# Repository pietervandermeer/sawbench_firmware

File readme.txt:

The Sawbench Synthesizer firmware.

(c) Tasty Chips Electronics, 2014-2016

This code may be used to update your sawbench synth, using only an Arduino Uno 
(10 euro from China). The easiest way of doing things is to: 

1) install this archive in your arduino folder. On Mac that's mostly 
~/Documents/Arduino

2) start Arduino IDE

3) open sawbench_v3/sawbench_v3.ino

4) attach your arduino uno

5) upload. The firmware is now present on the Arduino's Atmega328P. 

6) open up the sawbench, and remove its atmega. 

7) replace the sawbench's Atmega with the one from the Arduino. Presto!

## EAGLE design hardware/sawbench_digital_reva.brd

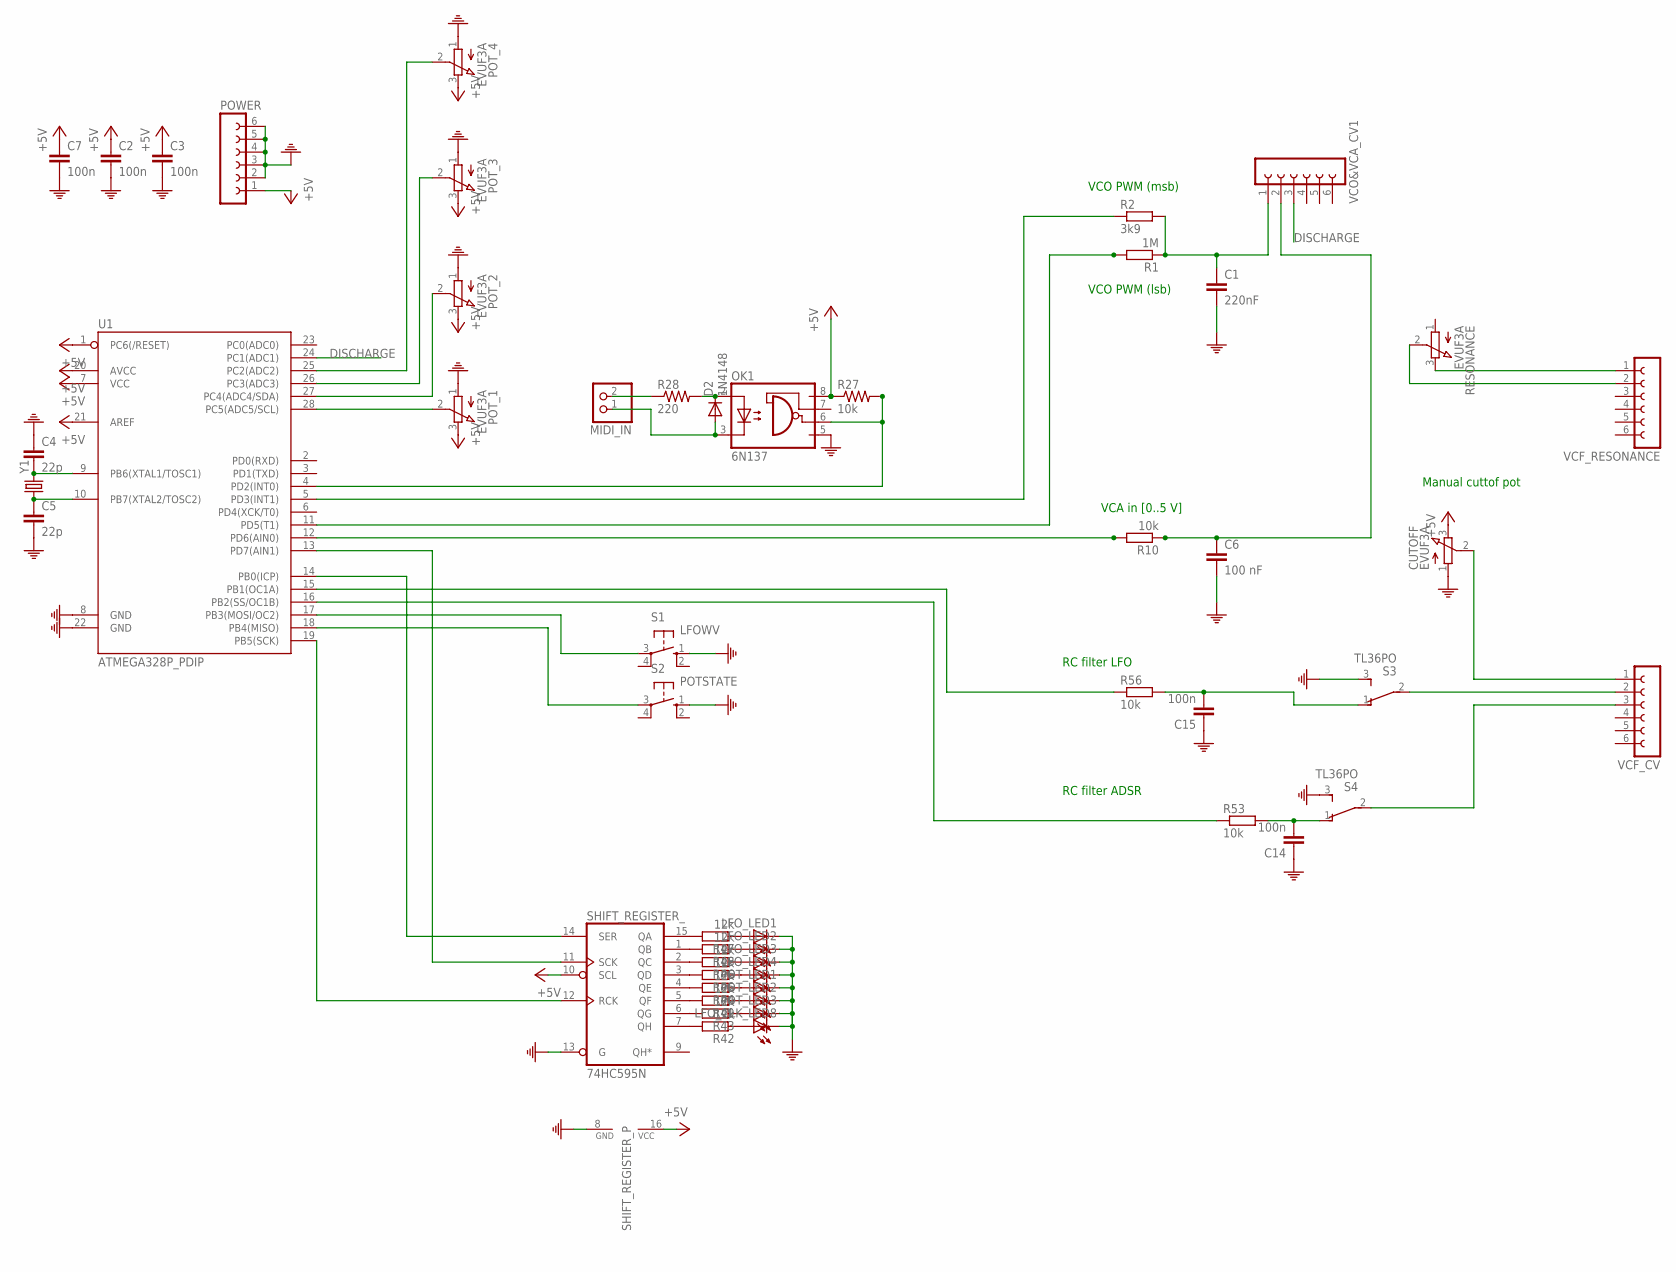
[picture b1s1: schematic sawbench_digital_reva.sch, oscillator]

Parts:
C1: 220nF; C050-024X044
C2, C3, C7, C14, C15: 100n; C025-024X044
C4, C5: 22p; C025-024X044
C6: 100 nF; C025-025X050
CUTOFF: EVUF3A; EVUF
D2: 1N4148; D-5
LFO_CLK_LED8: LED3MM
LFO_LED1, LFO_LED2, LFO_LED3, LFO_LED4: LED3MM
MIDI_IN: PINHD-1X2; 1X02
OK1: 6N137; DIL08
POT_1, POT_2, POT_3, POT_4: EVUF3A; EVUF
POT_LED1, POT_LED2, POT_LED3: LED3MM
POWER: FE06-1; FE06
R1: 1M; 0204/7
R2: 3k9; 0204/7
R10, R27, R53, R56: 10k; 0204/7
R28: 220; 0204/7
R42, R43, R44, R45, R46, R47, R48, R49: 12k; 0204/7
RESONANCE: EVUF3A; EVUF
S1: LFOWV; B3F-10XX(TASTYSWITCH)
S2: POTSTATE; B3F-10XX(TASTYSWITCH)
S3, S4: TL36PO; TL3XPO(TASTY_CHIPS_UPDATE)
SHIFT_REGISTER_: 74HC595N; DIL16
U1: ATMEGA328P_PDIP; DIL28-3
VCF_CV: FE06-1; FE06
VCF_RESONANCE: FE06-1; FE06
VCO&VCA_CV1: FE06-1; FE06
Y1: CRYSTALHC49S; HC49/S

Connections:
+5V: C2.1, C3.1, C7.1, CUTOFF.3 (E), OK1.8 (VCC), POT_1.3 (E), POT_2.3 (E), POT_3.3 (E), POT_4.3 (E), POWER.1, R27.1, SHIFT_REGISTER_.10 (SCL), SHIFT_REGISTER_.16 (VCC), U1.1 (PC6(/RESET)), U1.7 (VCC), U1.20 (AVCC), U1.21 (AREF)
DISCHARGE: U1.24 (PC1(ADC1)), VCO&VCA_CV1.3
unnamed: C1.1, R1.1, R2.2, VCO&VCA_CV1.1
unnamed: C6.1, R10.1, VCO&VCA_CV1.2
unnamed: R1.2, U1.11 (PD5(T1))
unnamed: S3.2, VCF_CV.2
unnamed: S4.2, VCF_CV.3
unnamed: OK1.6 (VO), R27.2, U1.4 (PD2(INT0))
unnamed: R2.1, U1.5 (PD3(INT1))
unnamed: POT_1.2 (S), U1.28 (PC5(ADC5/SCL))
unnamed: POT_4.2 (S), U1.25 (PC2(ADC2))
unnamed: POT_2.2 (S), U1.27 (PC4(ADC4/SDA))
unnamed: SHIFT_REGISTER_.11 (SCK), U1.13 (PD7(AIN1))
unnamed: POT_3.2 (S), U1.26 (PC3(ADC3))
unnamed: S1.3, U1.17 (PB3(MOSI/OC2))
unnamed: C4.2, U1.9 (PB6(XTAL1/TOSC1)), Y1.2
unnamed: C5.1, U1.10 (PB7(XTAL2/TOSC2)), Y1.1
unnamed: R10.2, U1.12 (PD6(AIN0))
unnamed: CUTOFF.2 (S), VCF_CV.1
unnamed: D2.C, OK1.2 (A), R28.2
unnamed: MIDI_IN.2, R28.1
unnamed: LFO_LED1.A, R47.1
unnamed: RESONANCE.3 (E), VCF_RESONANCE.1
unnamed: C14.2, R53.2, S4.1 (O)
unnamed: R42.2, SHIFT_REGISTER_.7 (QH)
unnamed: R43.2, SHIFT_REGISTER_.6 (QG)
unnamed: R44.2, SHIFT_REGISTER_.4 (QE)
unnamed: R45.2, SHIFT_REGISTER_.3 (QD)
unnamed: R46.2, SHIFT_REGISTER_.2 (QC)
unnamed: R47.2, SHIFT_REGISTER_.15 (QA)
unnamed: R48.2, SHIFT_REGISTER_.1 (QB)
unnamed: R49.2, SHIFT_REGISTER_.5 (QF)
unnamed: LFO_LED2.A, R48.1
unnamed: LFO_LED3.A, R46.1
unnamed: LFO_LED4.A, R45.1
unnamed: POT_LED1.A, R44.1
unnamed: POT_LED2.A, R49.1
unnamed: POT_LED3.A, R43.1
unnamed: LFO_CLK_LED8.A, R42.1
unnamed: SHIFT_REGISTER_.12 (RCK), U1.19 (PB5(SCK))
unnamed: SHIFT_REGISTER_.14 (SER), U1.14 (PB0(ICP))
unnamed: S2.3, U1.18 (PB4(MISO))
unnamed: C15.2, R56.2, S3.1 (O)
unnamed: R56.1, U1.15 (PB1(OC1A))
unnamed: R53.1, U1.16 (PB2(SS/OC1B))
unnamed: RESONANCE.2 (S), VCF_RESONANCE.2
unnamed: D2.A, MIDI_IN.1, OK1.3 (C)
PE: C1.2, C2.2, C3.2, C4.1, C5.2, C6.2, C7.2, C14.1, C15.1, CUTOFF.1 (A), LFO_CLK_LED8.K (C), LFO_LED1.K (C), LFO_LED2.K (C), LFO_LED3.K (C), LFO_LED4.K (C), OK1.5 (GND), POT_1.1 (A), POT_2.1 (A), POT_3.1 (A), POT_4.1 (A), POT_LED1.K (C), POT_LED2.K (C), POT_LED3.K (C), POWER.2, POWER.3, POWER.4, POWER.5, POWER.6, S1.1 (S), S2.1 (S), S3.3 (S), S4.3 (S), SHIFT_REGISTER_.8 (GND), SHIFT_REGISTER_.13 (G), U1.8 (GND), U1.22 (GND)

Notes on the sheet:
VCO PWM (msb)
VCO PWM (lsb)
VCA in [0..5 V]
RC filter LFO
RC filter ADSR
Manual cuttof pot

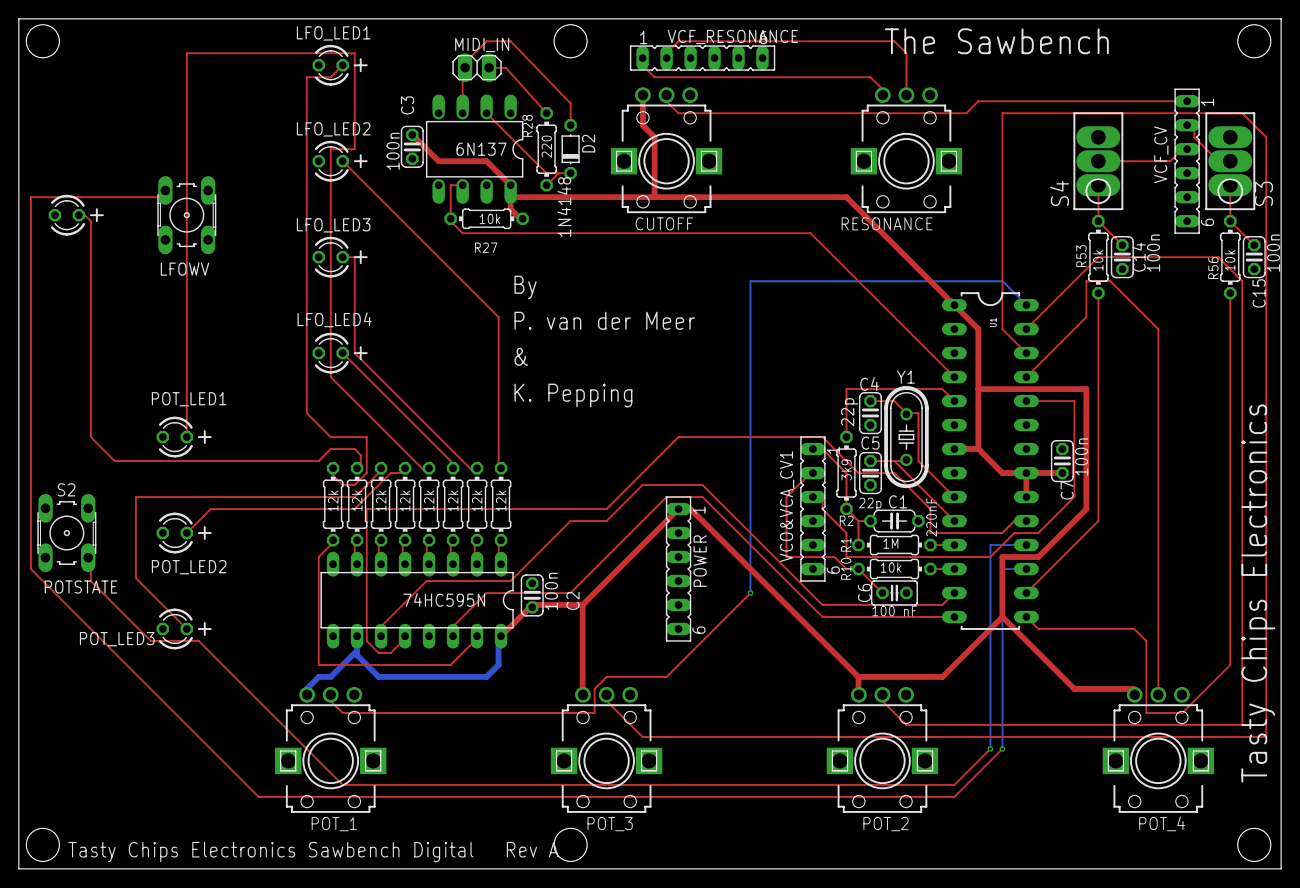
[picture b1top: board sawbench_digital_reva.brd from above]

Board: 2 copper layers, 133.7 x 90.0 mm, 52 parts (0 on the bottom side), 48 nets.

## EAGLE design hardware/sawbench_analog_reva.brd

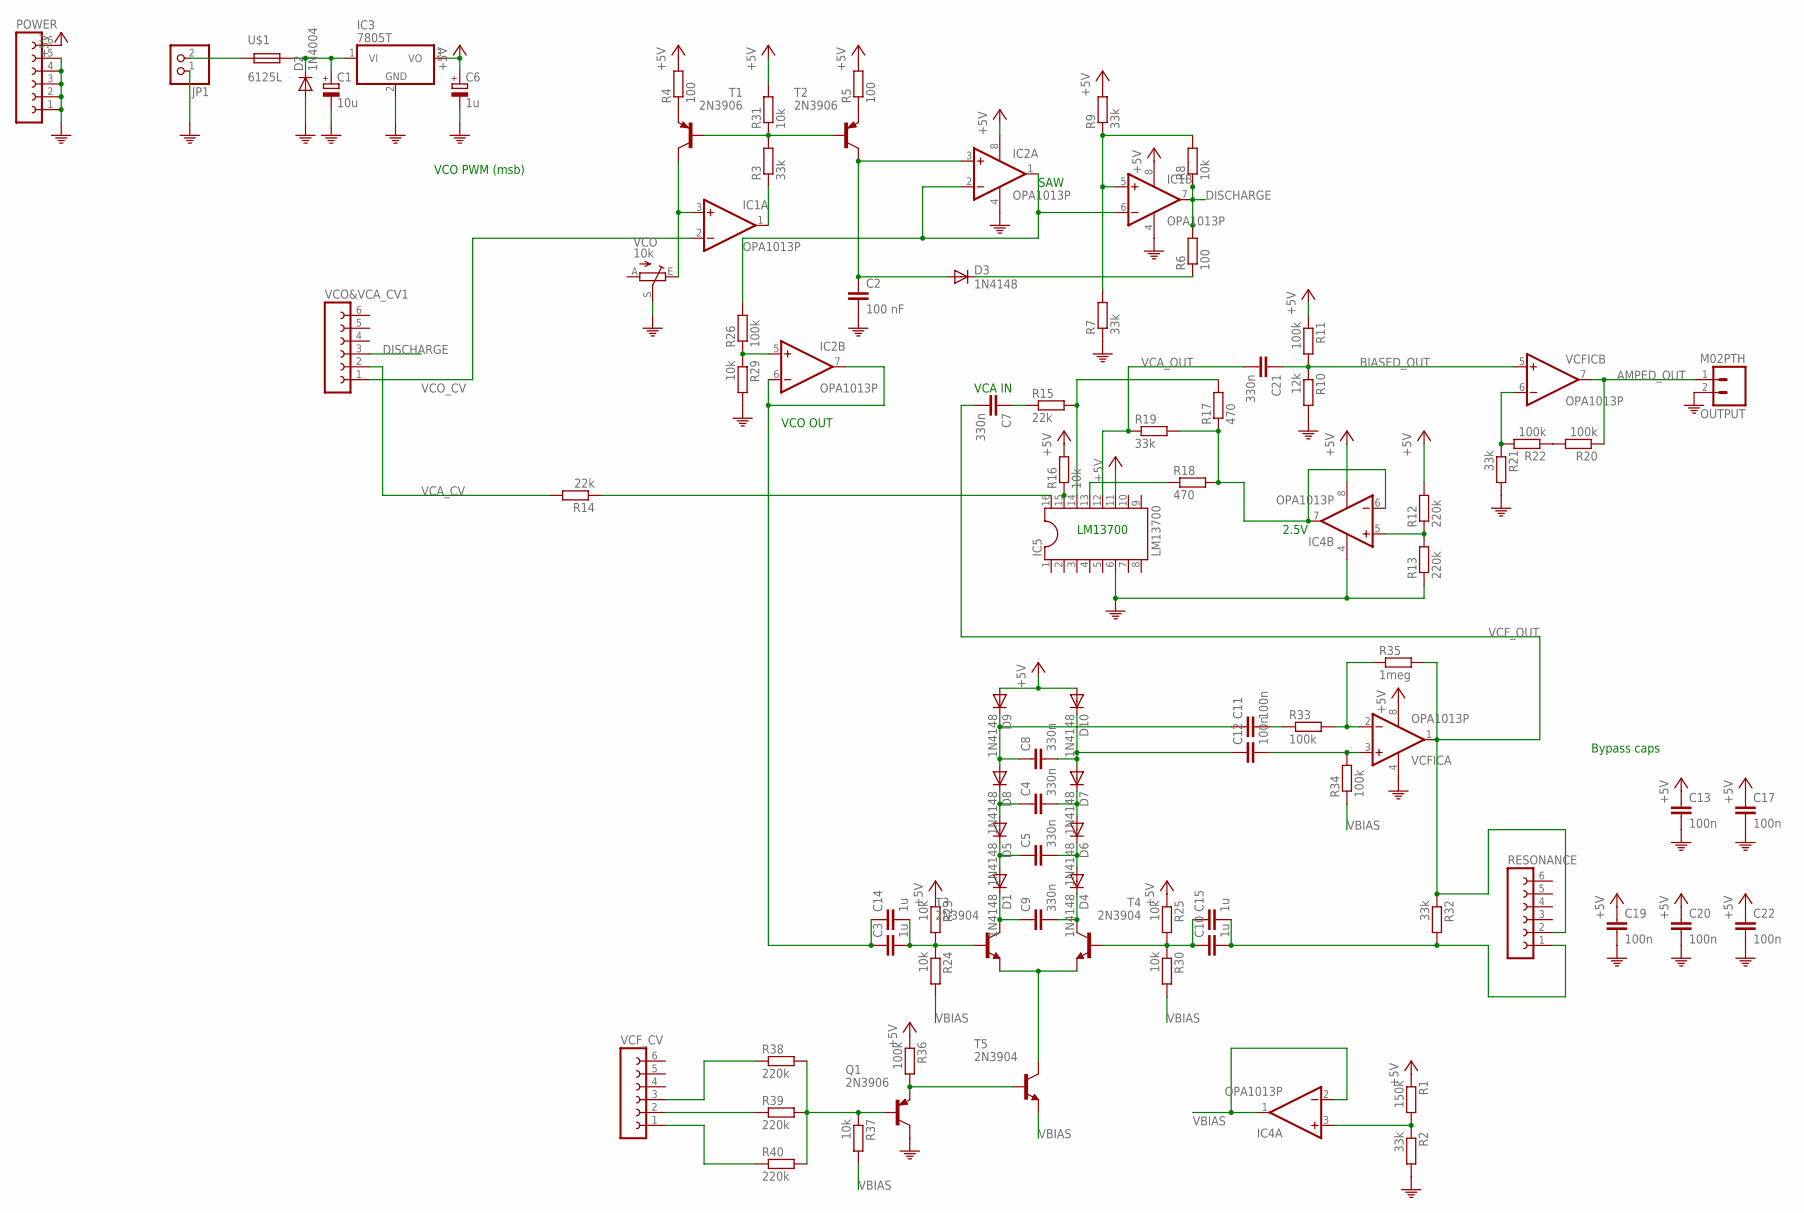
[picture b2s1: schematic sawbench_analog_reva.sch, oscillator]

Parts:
C1: 10u; E2,5-6
C2: 100 nF; C050-030X075
C3, C10, C14, C15: 1u; C050-024X044
C4, C5, C8, C9: 330n; C050-030X075
C6: 1u; E2,5-6
C7, C21: 330n; C050-024X044
C11, C12: 100n; C050-025X075
C13, C17, C19, C20, C22: 100n; C025-024X044
D1, D3, D4, D5, D6, D7, D8, D9, D10: 1N4148; D-5
D2: 1N4004; DO41-10
IC1, IC2, IC4: OPA1013P; DIL08
IC3: 7805T; TO220H
IC5: LM13700; DIL16
JP1: PINHD-1X2; 1X02
OUTPUT: M02PTH; 1X02
POWER: FE06-1; FE06
Q1: 2N3906; TO92-EBC
R1: 150k; 0204/7
R2, R3, R7, R9, R19, R21, R32: 33k; 0204/7
R4, R5, R6: 100; 0204/7
R8, R16, R23, R24, R25, R29, R30, R31, R37: 10k; 0204/7
R10: 12k; 0204/7
R11, R20, R22, R26, R33, R34, R36: 100k; 0204/7
R12, R13, R38, R39, R40: 220k; 0204/7
R14, R15: 22k; 0204/7
R17, R18: 470; 0204/7
R35: 1meg; 0204/7
RESONANCE: FE06-1; FE06
T1, T2: 2N3906; TO92-EBC
T3, T4, T5: 2N3904; TO92-EBC
U$1: 6125L
VCFIC: OPA1013P; DIL08
VCF_CV: FE06-1; FE06
VCO: 10k; RJ9W
VCO&VCA_CV1: FE06-1; FE06

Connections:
+5V: C6.+, C13.1, C17.1, C19.1, C20.1, C22.1, D9.A, D10.A, IC1.8 (V+), IC2.8 (V+), IC3.3 (VO), IC4.8 (V+), IC5.11, POWER.6, R1.1, R4.2, R5.2, R9.2, R11.1, R12.2, R16.2, R23.1, R25.1, R31.2, R36.1, VCFIC.8 (V+)
AMPED_OUT: OUTPUT.1, R20.1, VCFIC.7 (OUT)
BIASED_OUT: C21.1, R10.1, R11.2, VCFIC.5 (+IN)
DISCHARGE: IC1.7 (OUT), R6.2, R8.1, VCO&VCA_CV1.3
unnamed: R20.2, R22.1
unnamed: IC1.3 (+IN), T1.C, VCO.E
unnamed: C3.1, C14.1, IC2.6 (-IN), IC2.7 (OUT)
unnamed: C2.1, D3.A, IC2.3 (+IN), T2.C
unnamed: IC1.1 (OUT), R3.1
unnamed: R3.2, R31.1, T1.B, T2.B
unnamed: R4.1, T1.E
unnamed: R5.1, T2.E
unnamed: IC5.16, R14.1
unnamed: IC1.6 (-IN), IC2.1 (OUT), IC2.2 (-IN), R26.2
unnamed: R40.1, VCF_CV.1
unnamed: R39.1, VCF_CV.2
unnamed: IC1.5 (+IN), R7.2, R8.2, R9.1
unnamed: JP1.2, U$1.P$1 (1)
unnamed: D3.C, R6.1
unnamed: R38.1, VCF_CV.3
unnamed: IC4.3 (+IN), R1.2, R2.1
unnamed: IC4.5 (+IN), R12.1, R13.2
unnamed: IC5.13, R18.1
unnamed: IC5.14, R15.2, R17.2
unnamed: IC5.15, R16.1
unnamed: R21.1, R22.2, VCFIC.6 (-IN)
unnamed: IC4.6 (-IN), IC4.7 (OUT), R17.1, R18.2, R19.2
unnamed: C3.2, C14.2, R23.2, R24.1, T3.B
unnamed: T3.E, T4.E, T5.C
unnamed: C9.1, D1.C, T3.C
unnamed: C9.2, D4.C, T4.C
unnamed: C5.1, D1.A, D5.C
unnamed: C1.+, D2.C, IC3.1 (VI), U$1.P$2 (2)
unnamed: IC2.5 (+IN), R26.1, R29.1
unnamed: C7.1, R15.1
unnamed: C4.1, D5.A, D8.C
unnamed: C8.1, C11.1, D8.A, D9.C
unnamed: C8.2, C12.1, D7.A, D10.C
unnamed: C4.2, D6.A, D7.C
unnamed: C5.2, D4.A, D6.C
unnamed: C10.1, C15.1, R25.2, R30.1, T4.B
unnamed: C10.2, C15.2, R32.2, RESONANCE.1
unnamed: C11.2, R33.1
unnamed: C12.2, R34.2, VCFIC.3 (+IN)
unnamed: R33.2, R35.1, VCFIC.2 (-IN)
unnamed: Q1.E, R36.2, T5.B
unnamed: Q1.B, R37.1, R38.2, R39.2, R40.2
PE: C1.-, C2.2, C6.-, C13.2, C17.2, C19.2, C20.2, C22.2, D2.A, IC1.4 (V-), IC2.4 (V-), IC3.2 (GND), IC4.4 (V-), IC5.6, JP1.1, OUTPUT.2, POWER.1, POWER.2, POWER.3, POWER.4, POWER.5, Q1.C, R2.2, R7.1, R10.2, R13.1, R21.2, R29.2, VCFIC.4 (V-), VCO.S
VBIAS: IC4.1 (OUT), IC4.2 (-IN), R24.2, R30.2, R34.1, R37.2, T5.E
VCA_CV: R14.2, VCO&VCA_CV1.2
VCA_OUT: C21.2, IC5.12, R19.1
VCF_OUT: C7.2, R32.1, R35.2, RESONANCE.2, VCFIC.1 (OUT)
VCO_CV: IC1.2 (-IN), VCO&VCA_CV1.1

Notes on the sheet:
VCO PWM (msb)
SAW
LM13700
2.5V
VCO OUT
VCA IN
Bypass caps

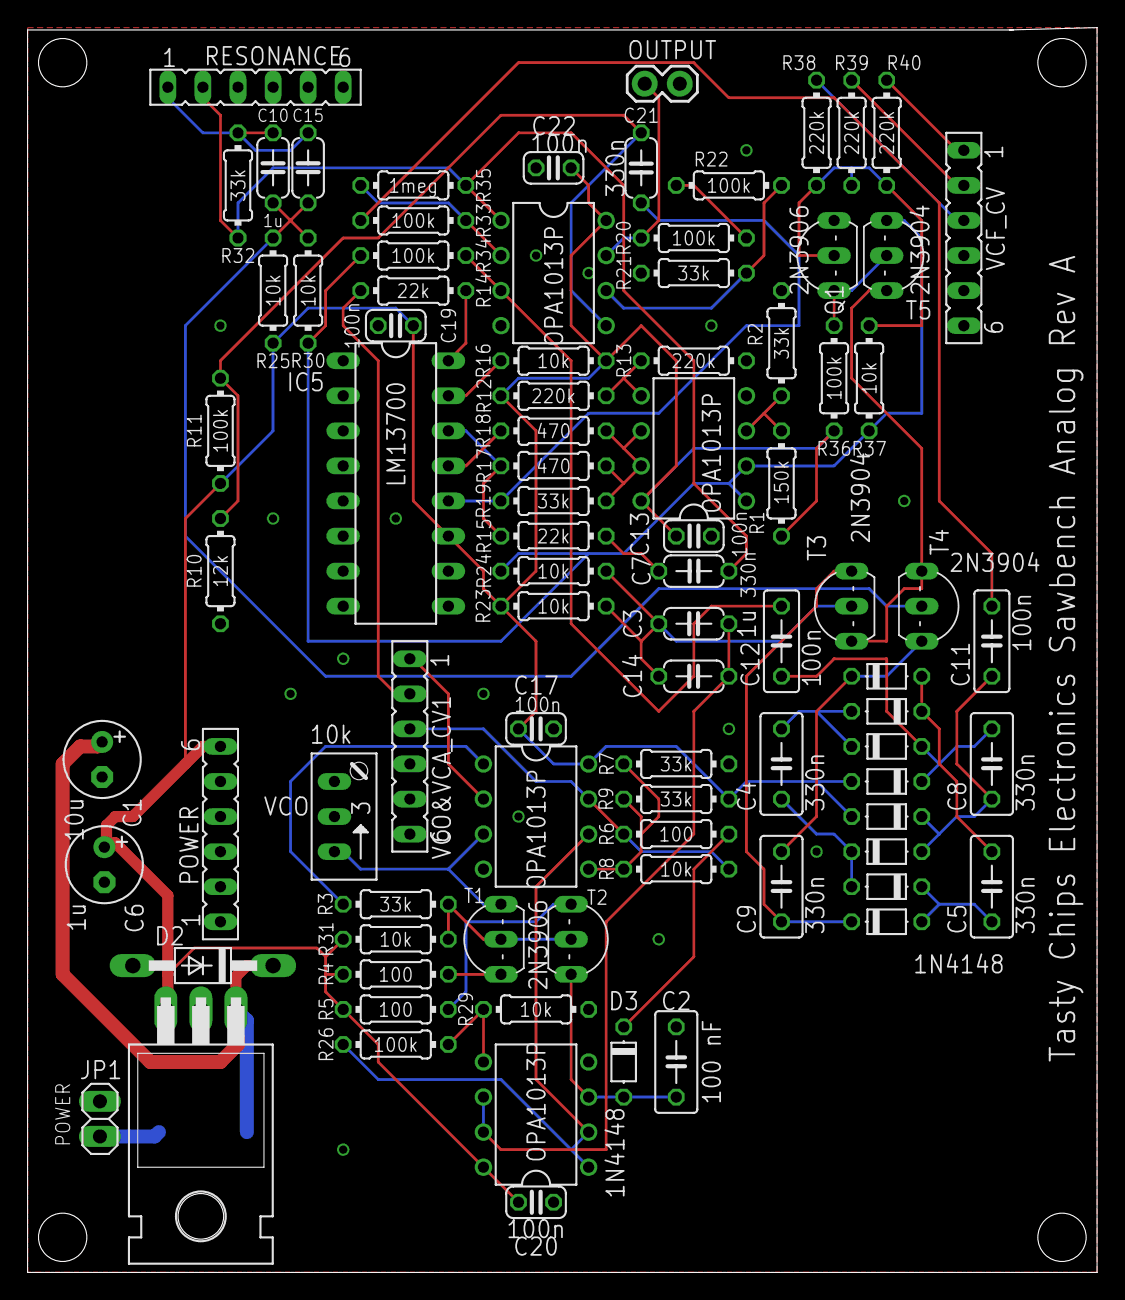
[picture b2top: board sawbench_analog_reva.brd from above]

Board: 2 copper layers, 77.5 x 90.2 mm, 88 parts (1 on the bottom side), 53 nets.

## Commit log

2014-12-20 initial commit, including koen's new sketch and PiggyLFO class.
2014-12-20 attempt to let MIDI and LFO not bite eachother.
2014-12-20 added VCF ENV. adapted Koen's LFO code to DDS in timed loop. MIDI IN seems fine again.
2015-01-09 lfo button pin changed. introduced gpio debugging again.
2015-01-18 unoptimized and non-midi version of sawbench firmware.
2015-01-18 optimized to one analogRead() using round robin.
2015-01-19 more optimized version _newer.ino.. still not good enough.
2015-01-19 a whattheheck. let's just run the loop at 1 kHz. oh yeah, pots now have nice negcube curves.
2015-01-19 callbacks for pot readouts.
2015-01-19 lfo speed for sample and hold.
2015-01-20 midi ccs for all 12 pot functions. vcf keyboard tracking + midi cc. lfo led with soft pwm.
2015-01-20 fixed lfo crap. addressing with signed offset where unsigned is passed. yep.
2015-01-20 lfo speed via midi now scaled correctly.
2015-01-25 fixed potstate behaviour. midi can now always interrupt it. pots can always override midi, and their initial behavior after reset is fixed. lfo led now optional (because of the background noise it ma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
2015-01-25 and now for real.. pot+midi interaction has been fixed, for the last ultimate time. also the potstate code has been cleaned up and optimized.
2015-01-26 lfo type now selectable using midi.
2015-02-11 added calibration script for J unit.
2015-02-11 added lfo led disable featuring (hold down lfo button 3 seconds). added k unit calibration script.
2015-02-16 first version of the firmware that uses self-calibration. requires a trace (or patch wire) from vco buffer output to arduino pin 4.
2015-02-17 shortened calibration and also made it more reliable. boot now takes 3 seconds. parameters now have defaults. vcf env overflow bug fixed. lfo mode is sine wave, by default.
2015-02-20 introductory light show
2015-03-29 variable glide, legato (with cc on/off).
2015-03-30 looping adsr, independent for vca and vcf. config via cc. sustain is skipped when looping.
2015-04-17 added sawbench_v3.ino.. lol.
2015-07-24 potential fix for midi problems. all midi bytes are now handled by the statemachine, at least.
2015-08-19 added readme.txt with installation details. added history.txt.
2016-01-05 new adsr curve and precision: shorter attacks, while retaining full adsr range. exponential adsr as well. unit tests check out fine, fw compiles. not yet tested live..
2016-10-05 midi beat fix.
2016-10-05 updated some ascii.
2016-10-07 debugged v1.2. exponential envelopes work perfectly, and controllable by cc. steplut in program memory.
2018-11-04 hardware added

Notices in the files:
parts and their libraries:
SparkFun-Connectors: Licensing: Creative Commons ShareAlike 4.0 International - https://creativecommons.org/licenses/by-sa/4.0
